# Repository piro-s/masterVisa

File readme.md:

# MasterVisa:  
Project for business card  

### Schemes:  
###### masterVisa_v0.1:  
[pdf](docs/masterVisa_v0.1.pdf)  

### Images:  
###### masterVisa_v0.2:  
top:  
  
bottom:  

###### gerber:  
Archive for production:  
[masterVisa_v0.2](https://github.com/piro-s/masterVisa/raw/main/gerber/masterVisa_v0.2_2024_04_29.zip)

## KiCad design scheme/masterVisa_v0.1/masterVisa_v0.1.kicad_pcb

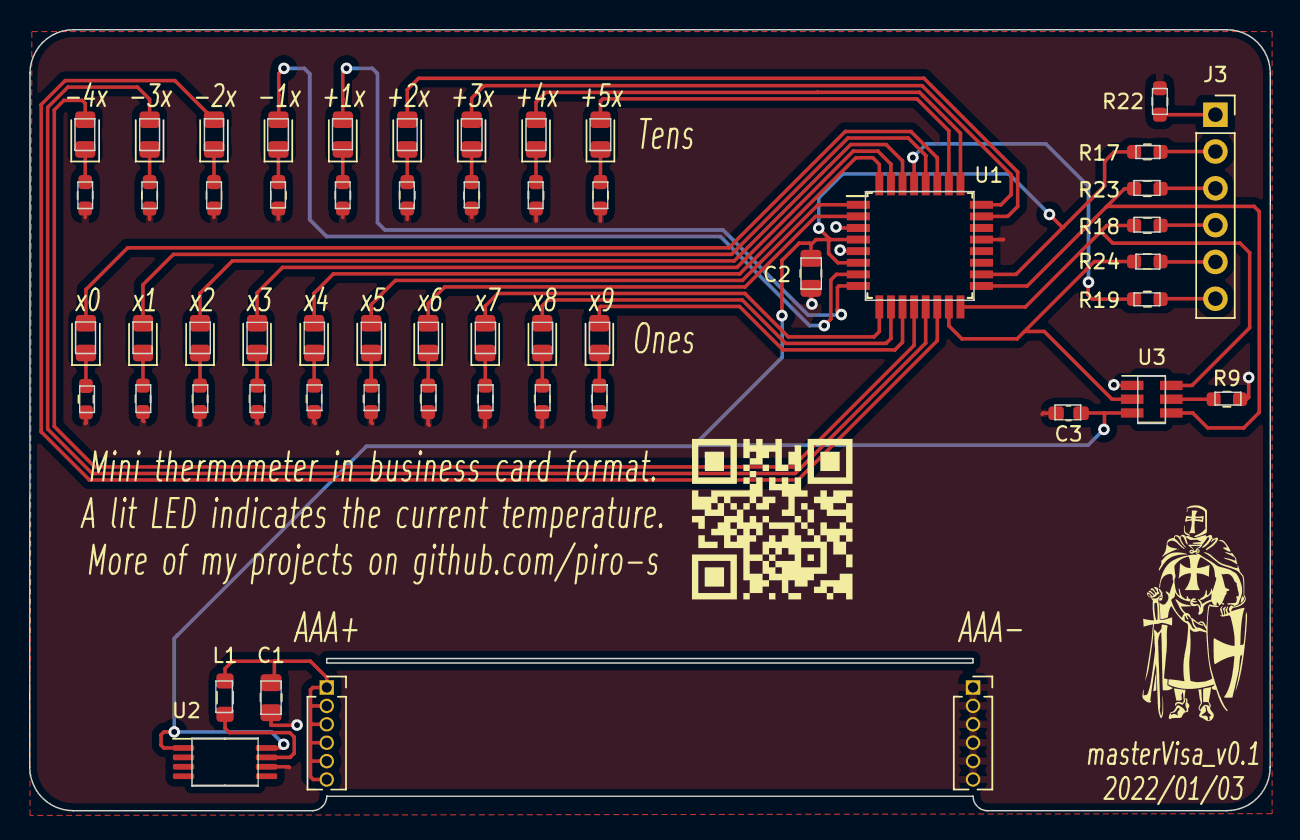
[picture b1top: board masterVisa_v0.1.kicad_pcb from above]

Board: 2 copper layers, 85.6 x 53.9 mm, 55 parts (0 on the bottom side), 53 nets.

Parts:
C1, C2: 10uF; C_0805_2012Metric_Pad1.18x1.45mm_HandSolder
C3: 100n; C_0603_1608Metric_Pad1.08x0.95mm_HandSolder
D1, D4, D6, D8: BLUE; LED_0805_2012Metric_Pad1.15x1.40mm_HandSolder
D2, D3, D5, D7, D9, D11, D13, D15, D17, D19: YEL; LED_0805_2012Metric_Pad1.15x1.40mm_HandSolder
D10, D12: GREEN; LED_0805_2012Metric_Pad1.15x1.40mm_HandSolder
D14, D16, D18: RED; LED_0805_2012Metric_Pad1.15x1.40mm_HandSolder
J1: AAA+; PinSocket_1x06_P1.27mm_Vertical
J2: AAA-; PinSocket_1x06_P1.27mm_Vertical
J3: USBAsp; PinSocket_1x06_P2.54mm_Vertical
L1: 10uH; L_0805_2012Metric_Pad1.05x1.20mm_HandSolder
R1, R2, R3, R4, R5, R6, R7, R8, R10, R11, R12, R13, R14, R15, R16, R20, R21, R25, R26: 300; R_0603_1608Metric_Pad0.98x0.95mm_HandSolder
R9: 0R; R_0603_1608Metric_Pad0.98x0.95mm_HandSolder
R17, R18, R19, R24: 10R; R_0603_1608Metric_Pad0.98x0.95mm_HandSolder
R22, R23: 1R8; R_0603_1608Metric_Pad0.98x0.95mm_HandSolder
U1: ATmega48-20A; TQFP-32_7x7mm_P0.8mm
U2: L6920; TSSOP-8_4.4x3mm_P0.65mm
U3: ADT7301; SOT-23-6_Handsoldering

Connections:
+3V3: C2.1, C3.1, R17.1, U1.4 (VCC), U1.6 (VCC), U1.18 (AVCC), U2.1 (FB), U2.8 (OUT), U3.3 (Vdd)
/MISO: R18.1, U1.16 (PB4), U3.6 (Dout)
/MOSI: R24.1, U1.15 (PB3), U3.2 (Din)
/RESET: R19.1, U1.29 (~RESET/PC6)
/SCK: R23.1, U1.17 (PB5), U3.4 (SCK)
/temp_0: D2.2 (A), U1.27 (PC4)
/temp_1: D3.2 (A), U1.28 (PC5)
/temp_2: D5.2 (A), U1.30 (PD0)
/temp_3: D7.2 (A), U1.31 (PD1)
/temp_4: D9.2 (A), U1.32 (PD2)
/temp_5: D11.2 (A), U1.1 (PD3)
/temp_6: D13.2 (A), U1.2 (PD4)
/temp_7: D15.2 (A), U1.9 (PD5)
/temp_8: D17.2 (A), U1.10 (PD6)
/temp_9: D19.2 (A), U1.11 (PD7)
/temp_10: D10.2 (A), U1.8 (XTAL2/PB7)
/temp_20: D12.2 (A), U1.23 (PC0)
/temp_30: D14.2 (A), U1.24 (PC1)
/temp_40: D16.2 (A), U1.25 (PC2)
/temp_50: D18.2 (A), U1.26 (PC3)
/temp_-10: D8.2 (A), U1.7 (XTAL1/PB6)
/temp_-20: D6.2 (A), U1.14 (PB2)
/temp_-30: D4.2 (A), U1.13 (PB1)
/temp_-40: D1.2 (A), U1.12 (PB0)
GND: C1.2, C2.2, C3.2, J2.1, J2.2, J2.3, J2.4, J2.5, J2.6, R1.2, R2.2, R3.2, R4.2, R5.2, R6.2, R7.2, R8.2, R9.2, R10.2, R11.2, R12.2, R13.2, R14.2, R15.2, R16.2, R20.2, R21.2, R22.1, R25.2, R26.2, U1.3 (GND), U1.5 (GND), U1.21 (GND), U2.6 (GND), U3.1 (GND)
unnamed: C1.1, J1.1, J1.2, J1.3, J1.4, J1.5, J1.6, L1.1
unnamed: D1.1 (K), R1.1
unnamed: D2.1 (K), R2.1
unnamed: D3.1 (K), R3.1
unnamed: D4.1 (K), R4.1
unnamed: D5.1 (K), R5.1
unnamed: D6.1 (K), R6.1
unnamed: D7.1 (K), R7.1
unnamed: D8.1 (K), R8.1
unnamed: D9.1 (K), R10.1
unnamed: D10.1 (K), R11.1
unnamed: D11.1 (K), R12.1
unnamed: D12.1 (K), R13.1
unnamed: D13.1 (K), R14.1
unnamed: D14.1 (K), R15.1
unnamed: D15.1 (K), R16.1
unnamed: D16.1 (K), R20.1
unnamed: D17.1 (K), R21.1
unnamed: D18.1 (K), R25.1
unnamed: D19.1 (K), R26.1
unnamed: J3.1, R22.2
unnamed: J3.2, R17.2
unnamed: J3.3, R23.2
unnamed: J3.4, R18.2
unnamed: J3.5, R24.2
unnamed: J3.6, R19.2
unnamed: L1.2, U2.7 (LX)
unnamed: R9.1, U3.5 (CS)

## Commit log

2024-05-02 Initial
